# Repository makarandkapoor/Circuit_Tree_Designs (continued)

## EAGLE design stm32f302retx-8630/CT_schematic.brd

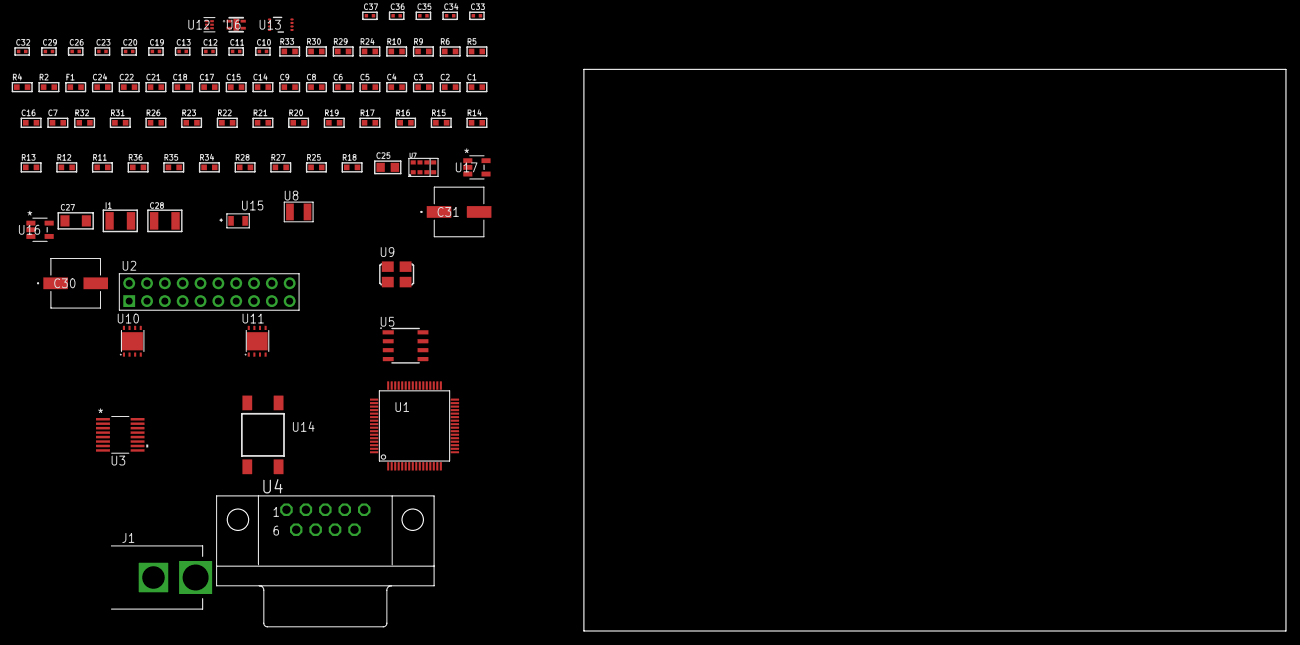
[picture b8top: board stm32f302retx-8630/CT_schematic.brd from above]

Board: 2 copper layers, 100.0 x 80.0 mm, 89 parts (0 on the bottom side), 51 nets, no tracks yet.

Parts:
C1, C9, C14, C15, C17, C18, C21, C22, C24: 1e-06; C0603
C2, C3, C4, C5, C6: 1e-07; C0603
C7: 4.7e-06; C0603
C8: 1e-08; C0603
C10, C11: 1e-11; C0402
C12, C13, C20, C29, C33, C35: 1e-07; C0402
C16: 2.2e-07; C0603
C19, C23, C26, C32, C34, C36, C37: 1e-08; C0402
C25: 1e-05; C0805
C27: 1e-05; C1206
C28: 1e-05; C1210
C30, C31: 0.0001; EXV-9H
F1: 240.0; L0603
I1: 1e-05; L1210
J1: PJ-037B; PJ-037B_PACKAGE
R2, R30: 1000.0; R0603
R4: 4700.0; R0603
R5, R6, R9, R10: 2200.0; R0603
R11, R12, R13, R14, R15, R16, R17, R19, R20, R21, R22, R23, R31, R32: 10000.0; R0603
R18, R25, R27, R28: 100000.0; R0603
R24: 22.0; R0603
R26: 36000.0; R0603
R29: 2231.0; R0603
R33: 9100.0; R0603
R34: 680000.0; R0603
R35: 120000.0; R0603
R36: 200000.0; R0603
U1: STM32F302RET6; LQFP64
U2: TST-110-05-T-D-RA
U3: LTC2804CGN-1#PBF; SSOP-16
U4: 182-009-113R531; 182-009-MALE
U5: AT24C02D-SSHM-T; AT24C02D
U6: Si7034-A10-IM; SI7034-A10-IM
U7: TMD27711; SMD-8
U8: ABS07-32.768KHZ-7-T
U9: ASFL1-25MHZ-NCS; ASFL1
U10: LP2951ACSDX/NOPB; WSON-8
U11: LP3878SDX-ADJ/NOPB; WSON-8
U12: TPS3895ADRYR; SON-6
U13: LSF0102DCTR; DCU0008A_N
U14: 4-1437565-2; SW_4-1437565-2
U15: Q65110A2395; LGM67K-G1J2-24-Z
U16, U17: nc7sz125m5x; NC7SZ125M5X

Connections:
CLK_CRYSTAL_U1_3: C10.1, U1.3, U8.1
CLK_CRYSTAL_U1_4: C11.1, U1.4, U8.2
CLK_U1_5: U1.5, U9.3
GND: C1.2, C2.2, C3.2, C4.2, C5.2, C6.2, C7.2, C8.2, C9.2, C10.2, C11.2, C12.2, C13.2, C14.2, C15.2, C17.2, C18.2, C19.2, C20.2, C21.2, C22.2, C23.2, C24.2, C25.2, C26.2, C27.2, C28.2, C29.2, C30.2, C31.2, C32.2, C33.2, C34.2, C35.2, C36.2, C37.2, J1.2, R2.2, R11.2, R17.2, R19.2, R21.2, R22.2, R27.2, R30.2, R33.2, R35.2, U1.12, U1.18, U1.31, U1.47, U1.63, U2.4, U2.6, U2.8, U2.10, U2.12, U2.14, U2.16, U2.18, U2.20, U3.8, U4.5, U5.4, U6.5, U7.3, U9.2, U10.3, U10.4, U10.PAD, U11.3, U11.PAD, U12.2, U13.1, U15.C, U16.2, U16.3, U17.1, U17.3
NET_U1_7: R4.1, U1.7, U17.4
NET_U1_13: C8.1, C9.1, F1.1, U1.13
NET_U1_40: R10.1, U1.40, U5.5
NET_U1_41: R9.1, U1.41, U5.6
NET_U1_58: R5.1, U1.58, U7.2
NET_U1_59: R6.1, U1.59, U7.8
NET_U1_60: R11.1, U1.60
NET_U1_62: U14.3, U14.4
NET_U2_19: R17.1, U2.19
NET_U3_6: C14.1, U3.6
NET_U3_7: C16.1, I1.2, U3.7
NET_U3_9: C15.1, U3.9
NET_U3_10: C16.2, U3.10
NET_U3_11: R18.1, U3.11
NET_U4_2: U3.1, U4.2
NET_U4_3: U3.3, U4.3
NET_U4_7: U3.2, U4.7
NET_U4_8: U3.4, U4.8
NET_U5_1: R20.1, U5.1
NET_U5_2: R21.1, U5.2
NET_U5_3: R22.1, U5.3
NET_U5_7: R19.1, U5.7
NET_U7_4: C22.1, R24.1, U7.4
NET_U7_7: R23.1, U7.7
NET_U10_5: R25.1, U10.5
NET_U10_7: R26.2, R27.1, U10.7
NET_U11_1: C26.1, U11.1
NET_U11_6: R29.2, R30.1, U11.6
NET_U11_8: R28.1, U11.8
NET_U12_1: R32.1, R33.1, U12.1
NET_U12_3: R34.2, R35.1, U12.3
NET_U12_4: R31.1, U12.4, U16.4, U17.2
NET_U13_8: R36.1, U13.8
NET_U14_1: R2.1, U14.1, U14.2
PROC_I2C2_SCL_TOXCVR: U6.2, U13.5
PROC_I2C2_SDA_TOXCVR: U6.4, U13.6
PROC_SYS_JTCK_SWCLK: R15.1, U1.49, U2.9
PROC_SYS_JTDI: R13.1, U1.50, U2.5
PROC_SYS_JTDO_TRACESWO: U1.55, U2.13
PROC_SYS_JTMS_SWDIO: R14.1, U1.46, U2.7
PROC_SYS_NJTRST: R12.1, U1.56, U2.3
PROC_UART4_RX: U1.52, U3.16
PROC_UART4_TX: U1.51, U3.14
RST_OUT_U2_SRESET_B: R16.1, U2.15, U16.1
VCC_S1_8V2: C24.1, C27.1, C30.1, C31.1, J1.1, R28.2, U10.8, U11.4
VCC_TIER1_1V8: C17.1, C20.1, C25.1, C32.1, C33.1, C36.1, C37.1, I1.1, R18.2, R25.2, R26.1, R36.2, U3.5, U6.1, U10.1, U13.7, U16.5, U17.5
VCC_TIER1_3V3: C1.1, C2.1, C3.1, C4.1, C5.1, C6.1, C7.1, C12.1, C13.1, C18.1, C19.1, C21.1, C23.1, C28.1, C29.1, C34.1, C35.1, F1.2, R4.2, R5.2, R6.2, R9.2, R10.2, R12.2, R13.2, R14.2, R15.2, R16.2, R20.2, R23.2, R24.2, R29.1, R31.2, R32.2, R34.1, U1.1, U1.19, U1.32, U1.48, U1.64, U2.1, U2.2, U3.12, U5.8, U7.1, U9.4, U11.5, U12.6, U13.2
